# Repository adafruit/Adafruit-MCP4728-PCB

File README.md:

## Adafruit MCP4728 Quad 12-bit I2C DAC PCB

<a href="http://www.adafruit.com/products/4470"><br/>
Click here to purchase one from the Adafruit shop</a>

PCB files for the Adafruit MCP4728 Quad 12-bit I2C DAC. 

Format is EagleCAD schematic and board layout
* https://www.adafruit.com/product/4470

### Description

If you've ever said to yourself "Gee, I wish these four 12-bit DACs came in a single package with the ability to save their settings to an EEPROM", well I have good news. The MCP4728 is the answer to your wishes! Within it's little package, the MCP4728 has four, count em, four 12-bit DACs for whatever voltage setting needs you may have. In addition, it has the ability to store the settings for the DACs to an internal EEPROM so you can make like a Ronco Rotisserie and "set it and forget it". Once saved to the internal non-volatile memory, the settings will be loaded by default when the ADC powers up.

To take things even further, the MCP4728 lets you chose between two sources for your reference voltage: the input voltage that you use to power it on the VCC pin, or an internal 2.048V reference voltage. If you use the internal reference voltage (Vref in DAC speak) you can choose between 1X and 2X gain for the output, allowing your voltages to range from 0V to 2.048 or 0V- 4.096V as your application requires. 

By default you'll use the input voltage as your Vref, allowing you to scale the voltages from 0V-3.3V or 5V depending on your input voltage.o

The breakout for the MCP4728 is populated with the required support circuitry to use it with your microcontroller of choice or Blinka-supported computer. The oh-so-easy-to-use ed SparkFun Qwiic compatible STEMMA QT JST SH connectors ease the process of connecting the MCP4728 to your project and allows you to easily share an I2C bus with other STEMMA QT, Quiic, Grove or other compatible sensors.

Our drivers, wiring diagrams, and example code for Arduino, CircuitPython and Python make it easy to get started so you can get rolling with your project instead of futzing with figuring out how to wire things or get the code working. We've got you covered!

### License

Adafruit invests time and resources providing this open source design, please support Adafruit and open-source hardware by purchasing products from [Adafruit](https://www.adafruit.com)!

Designed by Limor Fried/Ladyada for Adafruit Industries.

Creative Commons Attribution/Share-Alike, all text above must be included in any redistribution. 
See license.txt for additional details.

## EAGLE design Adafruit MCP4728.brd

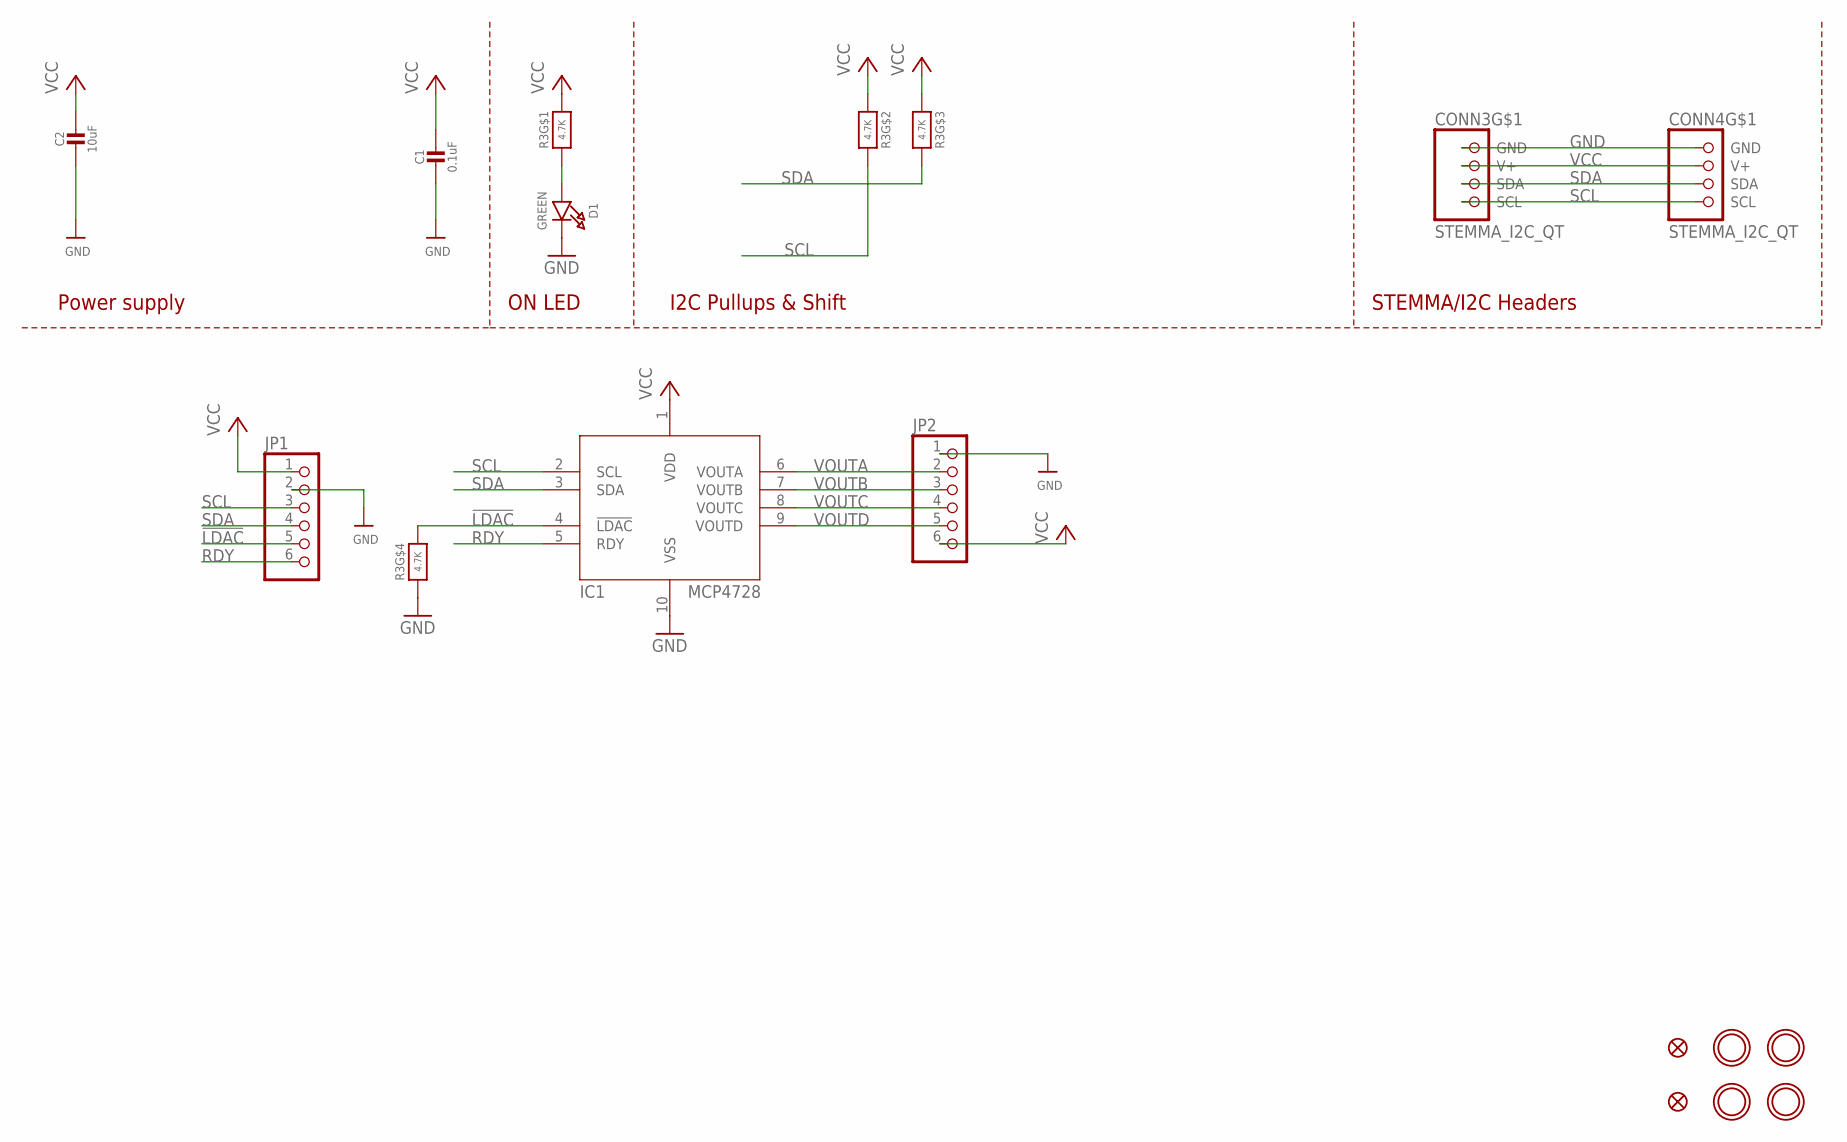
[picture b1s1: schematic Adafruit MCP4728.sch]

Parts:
C1: 0.1uF; 0603-NO
C2: 10uF; 0805-NO
CONN3, CONN4: STEMMA_I2C_QT; JST_SH4
D1: GREEN; CHIPLED_0603_NOOUTLINE
FID3, FID4: FIDUCIAL_1MM
IC1: MCP4728; MSOP10
JP1, JP2: HEADER-1X670MIL; 1X06_ROUND_70
R3: 4.7K; RESPACK_4X0603
U$1, U$17, U$19, U$21: MOUNTINGHOLE2.5; MOUNTINGHOLE_2.5_PLATED

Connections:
!LDAC: IC1.4 (!LDAC), JP1.5, R3.5 (2)
GND: C1.2, C2.2, CONN3.1 (GND), CONN4.1 (GND), D1.C, IC1.10 (VSS), JP1.2, JP2.1, R3.4 (1)
unnamed: D1.A, R3.1
RDY: IC1.5 (RDY), JP1.6
SCL: CONN3.4 (SCL), CONN4.4 (SCL), IC1.2 (SCL), JP1.3, R3.7 (2)
SDA: CONN3.3 (SDA), CONN4.3 (SDA), IC1.3 (SDA), JP1.4, R3.6 (2)
VCC: C1.1, C2.1, CONN3.2 (V+), CONN4.2 (V+), IC1.1 (VDD), JP1.1, JP2.6, R3.2 (1), R3.3 (1), R3.8 (2)
VOUTA: IC1.6 (VOUTA), JP2.2
VOUTB: IC1.7 (VOUTB), JP2.3
VOUTC: IC1.8 (VOUTC), JP2.4
VOUTD: IC1.9 (VOUTD), JP2.5

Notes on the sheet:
I2C Pullups & Shift
STEMMA/I2C Headers
ON LED
Power supply

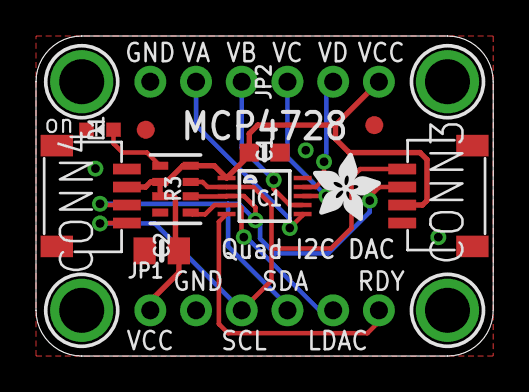
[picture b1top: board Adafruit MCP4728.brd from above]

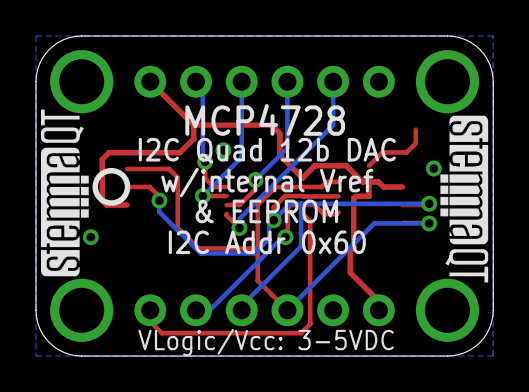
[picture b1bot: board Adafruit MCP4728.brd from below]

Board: 2 copper layers, 25.4 x 17.8 mm, 19 parts (3 on the bottom side), 11 nets.

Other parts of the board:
U$22: ADAFRUIT_3.5MM
U$25: PCBFEAT-REV-040
U$30, U$31: STEMMAQT

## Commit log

2020-09-07 Fixed product image

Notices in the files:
parts and their libraries:
microbuilder: This work is placed in the public domain, and may be freely used for commercial and non-commercial work with the following conditions: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
